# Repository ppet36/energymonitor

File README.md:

# Energy Monitor

This repository encapsulates one phase energy monitor for ThingSpeak based on ESP8266-01 module, current transformer and precision rectifier.

Because ESP8266-01 has only two digital I/O pins (and also for resolution) is for A/D conversion used 18bit I2C A/D converter MCP3421 and fullwave precision rectifier realized via double operational amplifier LM258. For measuring current is used current transformer 30A SCT-013-030 which has already integrated shunt resistor.

For powering is used miniature 3.3V/600mA power supply from eBay such as http://www.ebay.com/itm/400761809788, but due to initial power requirements of ESP8266 i recomend 3.3V/1A power supply (which is also available through this seller).

Repository contains CadSoft's Eagle schematic and PCB layout. Because i do not have equipment for proper handling of SMDs (and also for use MCP3421 on breadboard) i created small DPS that holds MCP3421 and has standard DIP dimensions.
Note: Some 100n capacitors is soldered directly to pins on bottom side of PCB.

Software can be uploaded to ESP8266 via Arduino IDE. For building you need MCP342x module which is available here https://github.com/uChip/MCP342X on GitHub. For first 5 minutes after module startup is available WiFi AP "EnergyMonitor" with HTTP server at 192.168.4.1:80 behind it. On this URL is available simple configuration page for setting WiFi parameters, ThingSpeak channel/field with write-key, mains voltage and other tunning parameters. After 5 minutes, when the page is not accessed, module starts automatically. After module connects to configured WiFi is configuration server available on internal network at DHCP assigned IP address. Default parameters can be set in source file.

There are also OpenSCAD and STL model for enclosure.

I use module for several months at home and also on cottage. My public channels on ThingSpeak are:

https://thingspeak.com/channels/150525

https://thingspeak.com/channels/157732

Here are some project images:

### PCBs

### Mounted PCB

### 3D printed case

### MCP3421 breadboard modules

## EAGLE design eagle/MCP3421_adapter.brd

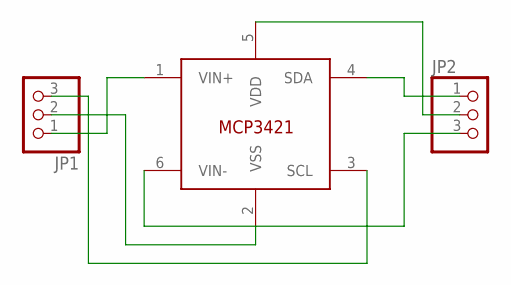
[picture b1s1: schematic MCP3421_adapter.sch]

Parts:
JP1, JP2: PINHD-1X3; 1X03
U$1: MCP3421; SOT23-6

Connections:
unnamed: JP1.1, U$1.1 (VIN+)
unnamed: JP1.2, U$1.2 (VSS)
unnamed: JP1.3, U$1.3 (SCL)
unnamed: JP2.1, U$1.4 (SDA)
unnamed: JP2.2, U$1.5 (VDD)
unnamed: JP2.3, U$1.6 (VIN-)

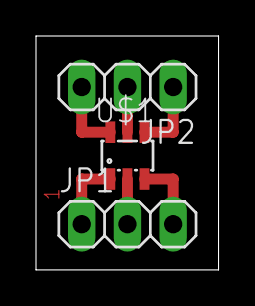
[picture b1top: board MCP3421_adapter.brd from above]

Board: 2 copper layers, 10.1 x 13.0 mm, 3 parts (0 on the bottom side), 6 nets.

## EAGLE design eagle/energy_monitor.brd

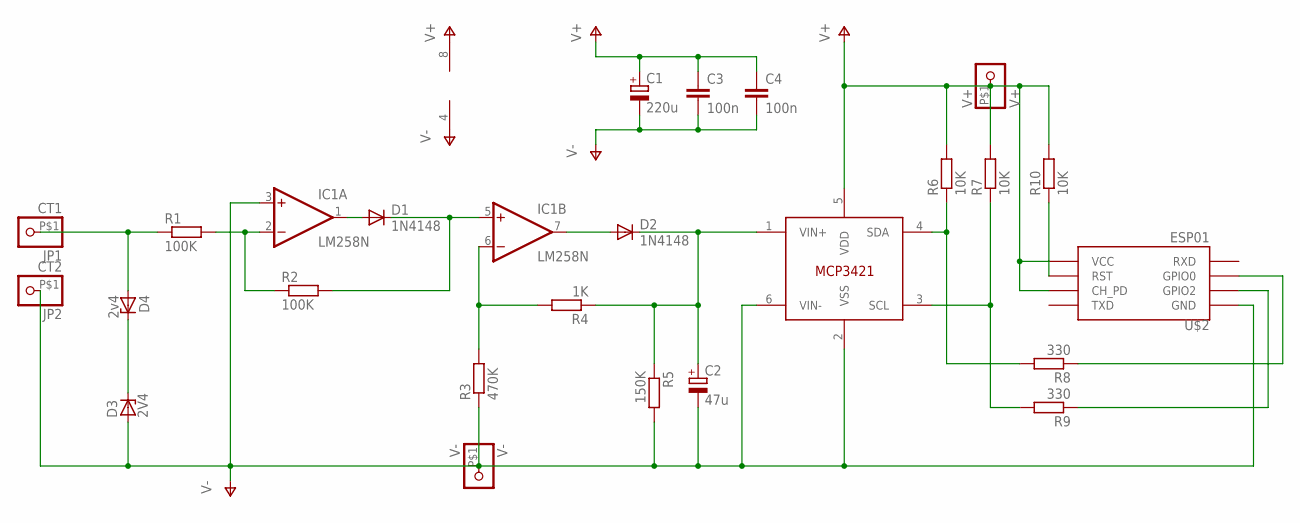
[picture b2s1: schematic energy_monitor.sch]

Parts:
C1: 220u; E2,5-6
C2: 47u; E2-4
C3, C4: 100n; C050-045X075
D1, D2: 1N4148; DO35-7
D3: 2V4; DO34Z7
D4: 2v4; DO34Z7
IC1: LM258N; DIL08
JP1: CT1; 1X1-BIGPOGO
JP2: CT2; 1X1-BIGPOGO
R1, R2: 100K; 0204/7
R3: 470K; 0204/7
R4: 1K; 0204/7
R5: 150K; 0204/7
R6, R7, R10: 10K; 0204/7
R8, R9: 330; 0204/7
U$1: MCP3421ADAPTER; DIL06
U$2: ESP01
V+: V+; 1X1-BIGPOGO
V-: V-; 1X1-BIGPOGO

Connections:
unnamed: D4.A, JP1.P$1, R1.1
unnamed: IC1.2 (-IN), R1.2, R2.1
unnamed: D1.A, IC1.1 (OUT)
unnamed: D1.C, IC1.5 (+IN), R2.2
unnamed: D3.C, D4.C
unnamed: D2.A, IC1.7 (OUT)
unnamed: C2.+, D2.C, R4.1, R5.1, U$1.1 (VIN+)
unnamed: IC1.6 (-IN), R3.2, R4.2
unnamed: R6.1, R8.2, U$1.4 (SDA)
unnamed: R7.1, R9.2, U$1.3 (SCL)
unnamed: R10.1, U$2.RST
unnamed: R8.1, U$2.GPIO0
unnamed: R9.1, U$2.GPIO2
V+: C1.+, C3.1, C4.1, IC1.8 (V+), R6.2, R7.2, R10.2, U$1.5 (VDD), U$2.CH_PD, U$2.VCC, V+.P$1
V-: C1.-, C2.-, C3.2, C4.2, D3.A, IC1.3 (+IN), IC1.4 (V-), JP2.P$1, R3.1, R5.2, U$1.2 (VSS), U$1.6 (VIN-), U$2.GND, V-.P$1

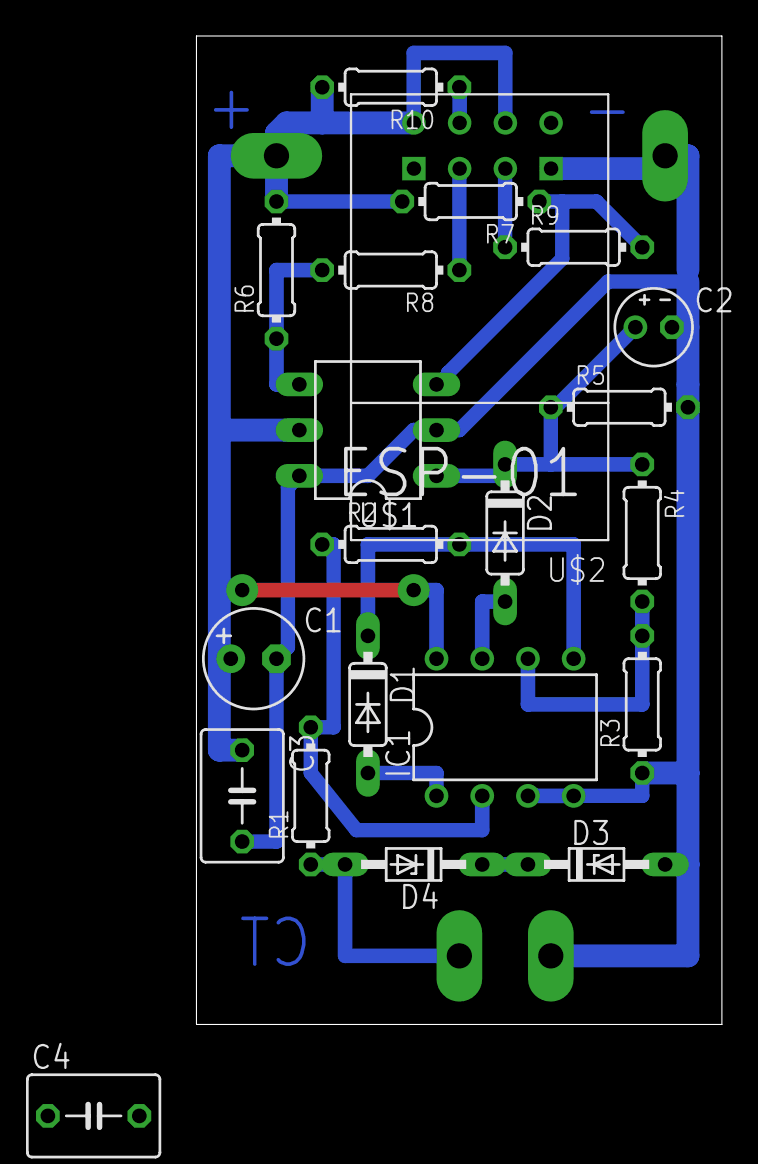
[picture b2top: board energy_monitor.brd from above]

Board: 2 copper layers, 29.2 x 54.9 mm, 25 parts (0 on the bottom side), 15 nets.
